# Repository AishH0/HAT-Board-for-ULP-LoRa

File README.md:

# ULP LoRa HAT PCB Design

The ULP LoRa HAT PCB is designed for 5V sensors to integrate with the ULP LoRa board. However, since the ULP LoRa only provides a 3.3V output voltage, 5V sensors cannot be directly integrated. This issue can be resolved by using a buck-boost converter or a boost converter circuit. In this PCB, the voltage is stepped up from 3.3V to 5V using a boost converter circuit with a TPS61202 IC. Level shifter (SN74LV1T34) is added for UART and GPIO peripherals.

# PCB Testing

- Short circuit test using Multimeter; No short ckt in the PCB.
- Provided 3.3V to the input side and Output voltage is noted (Needed output voltage is 5V); The output voltage is 6.5V.
- Varying the input voltage from 1V to 5V and the output voltage is
noted; The output voltage of the boost converter circuit is varying upto
6.5V (from the datasheet TPS61202 IC provides constant 5V.)
 - Varying the inductors and the output voltage is noted; Variable output
voltage is obtained.The PCB was modified using the TPS6120xEVM-179 datasheet. By varying the input voltage from 1V to 5V, the output voltage remains constant at 6.6V.

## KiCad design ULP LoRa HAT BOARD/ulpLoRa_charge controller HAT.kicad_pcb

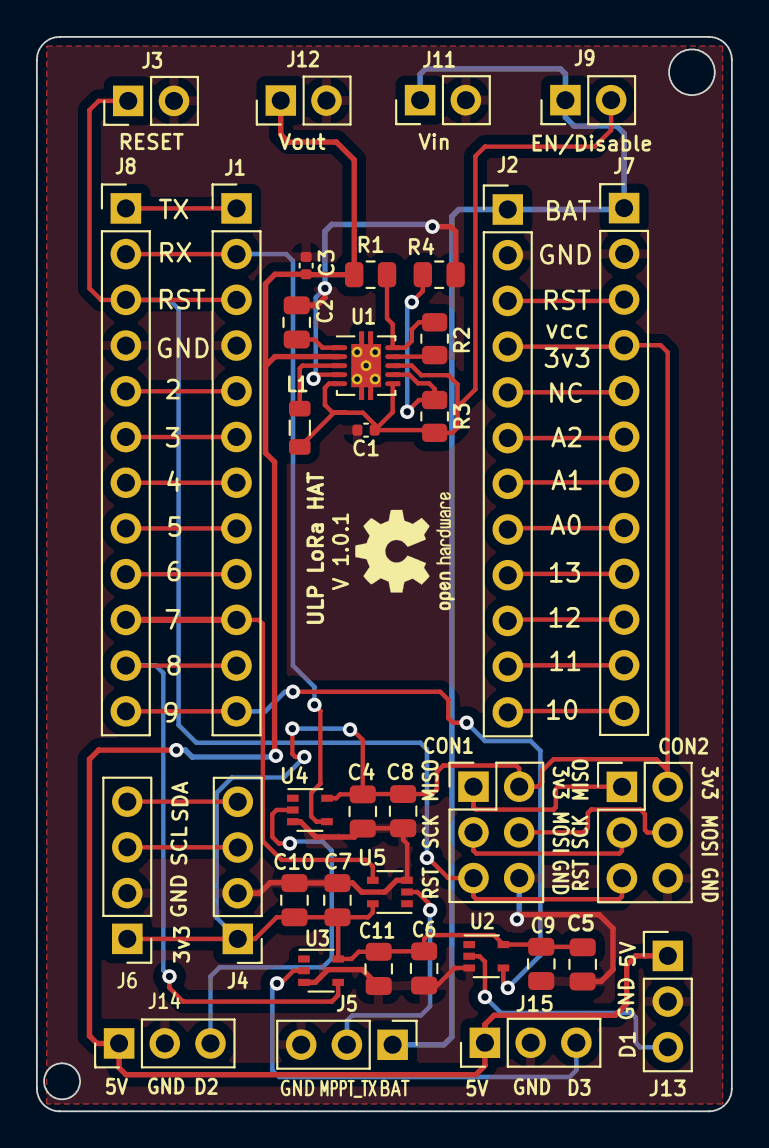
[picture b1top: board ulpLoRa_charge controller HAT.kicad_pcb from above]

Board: 2 copper layers, 38.6 x 59.7 mm, 38 parts (0 on the bottom side), 38 nets.

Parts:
C1, C3: 10uF; C_0402_1005Metric
C2, C4, C7, C9, C11: 0.1uF; C_0805_2012Metric
C5, C6, C8, C10: 1uF; C_0805_2012Metric
CON1, CON2: AVR-ISP-6; PinHeader_2x03_P2.54mm_Vertical
J1, J2: Conn_01x12; PinHeader_1x12_P2.54mm_Vertical
J3: RESET; PinHeader_1x02_P2.54mm_Vertical
J4, J6: I2C; PinHeader_1x04_P2.54mm_Vertical
J5, J13, J14, J15: Conn_01x03; PinHeader_1x03_P2.54mm_Vertical
J7, J8: Conn_01x12_Pin; PinHeader_1x12_P2.54mm_Vertical
J9: EN/Disable; PinHeader_1x02_P2.54mm_Vertical
J11: Vin; PinHeader_1x02_P2.54mm_Vertical
J12: Vout; PinHeader_1x02_P2.54mm_Vertical
L1: 2.2uH; L_0805_2012Metric
R1: 4.22M; R_0805_2012Metric
R2: 470K; R_0805_2012Metric
R3: 2.15M; R_0805_2012Metric
R4: 240K; R_0805_2012Metric
U1: TPS61202DRC; Texas_S-PVSON-N10_ThermalVias
U2, U3, U4, U5: SN74LV1T34DCK; SOT-353_SC-70-5
lg1: OSHW-Logo2_7.3x6mm_SilkScreen

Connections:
/5V: C3.2, J12.1, J13.1, J14.1, J15.1, R1.1, U1.2 (VOUT)
/7: J1.10, J8.10, U5.4 (Y)
/8: J1.11, J8.11, U3.4 (Y)
/9: J1.12, J8.12, U2.4 (Y)
/BAT: J2.1, J5.1, J7.1, J9.1, J11.1
/D1: J13.3, U2.2 (A)
/D2: J14.3, U4.2 (A)
/D3: J15.3, U3.2 (A)
/MISO: CON1.1, CON2.1
/MOSI: CON1.4, CON2.4
/MPPT_TX: J5.2, U5.2 (A)
/RST: CON1.5, CON2.5, J1.3, J3.1, J8.3
/RX: J1.2, J8.2, U4.4 (Y)
/SCK: CON1.3, CON2.3
/SCL: J4.3, J6.3
/SDA: J4.4, J6.4
/VCC: C4.1, C5.1, C6.1, C7.1, C8.1, C9.1, C10.1, C11.1, CON1.2, CON2.2, J2.4, J4.1, J6.1, J7.4, U2.5 (VCC), U3.5 (VCC), U4.5 (VCC), U5.5 (VCC)
GND: C1.1, C2.2, C3.1, C4.2, C5.2, C6.2, C7.2, C8.2, C9.2, C10.2, C11.2, CON1.6, CON2.6, J1.4, J2.2, J3.2, J4.2, J5.3, J6.2, J7.2, J8.4, J11.2, J12.2, J13.2, J14.2, J15.2, R2.2, R4.2, U1.4 (PGND), U1.9 (GND), U2.3 (GND), U3.3 (GND), U4.3 (GND), U5.3 (GND)
unnamed: J1.1, J8.1
unnamed: J1.5, J8.5
unnamed: J1.6, J8.6
unnamed: J1.7, J8.7
unnamed: J1.8, J8.8
unnamed: J1.9, J8.9
unnamed: J2.3, J7.3
unnamed: J2.5, J7.5
unnamed: J2.6, J7.6
unnamed: J2.7, J7.7
unnamed: J2.8, J7.8
unnamed: J2.9, J7.9
unnamed: J2.10, J7.10
unnamed: J2.11, J7.11
unnamed: J2.12, J7.12
unnamed: C1.2, J9.2, L1.1, R3.1, U1.5 (VIN), U1.6 (EN), U1.8 (PS)
unnamed: R1.2, R2.1, U1.10 (FB)
unnamed: L1.2, U1.3 (L)
unnamed: R3.2, R4.1, U1.7 (UVLO)
unnamed: C2.1, U1.1 (VAUX)

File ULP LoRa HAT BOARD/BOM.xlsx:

BILL OF MATERIALS
Item | Quantity | Reference | Value | PART TYPE | PCB Footprint | Manufacturer Part Number | Manfacturer Name | To be Procured by PCB Power | Remarks | Link
1 | 1 | U1 | IC REG BOOST 5V 1.2A 10VSON | Boost Converter | Boost Converter_SMD:10-VFDFN Exposed Pad | TPS61202DRCT | Texas Instruments | Yes |  | https://www.digikey.in/en/products/detail/texas-instruments/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
2 | 4 | U2, U3,U4, U5 | IC BUF NON-INVERT 5.5V SC70-5 | CMOS Logic level shifter | CMOS Logic Level shifter_SMD:SC-70-5 | SN74LV1T34DCKR | Texas Instruments | Yes |  | https://www.digikey.in/en/products/detail/texas-instruments/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
3 | 5 | C2, C4, C7, C9, C11 | 0.1 uF/10 V | Capacitor | Capacitor_SMD:C_0805_2012 Metric | C0805X104K8RACAUTO | KMET | yes |  | https://in.element14.com/kemet/c0805x104k8racauto/cap-mlcc-a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
4 | 4 | C6, C8, C5, C10 | 1 uF/10 V | Capacitor | Capacitor_SMD:C_0805_2012 Metric | C0805C105K8NACTU | KMET | yes |  | https://in.element14.com/kemet/c0805c105k8nactu/cap-1-f-10v-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
5 | 2 | C1, C3 | 10 uF/6.3 V | Capacitor | Capacitor_SMD:C_0402_1005 Metric | 490-GRM155R60J106ME05DCT-ND - Cut Tape (CT) | YAGEO | yes |  | https://www.digikey.in/en/products/detail/murata-electronics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
6 | 1 | R1 | 4.22 MOhms | Resistor | Resistor_SMD:R_0805_2012 Metric | CRCW08054M22FKEA | VISHAY | yes |  | https://www.mouser.in/ProductDetail/Vishay-Dale/CRCW08054M22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
7 | 1 | R2 | 470 Kohm | Resistor | Resistor_SMD:R_0805_2012 Metric | RCS0805470KJNEA | VISHAY | yes |  | https://www.mouser.in/ProductDetail/Vishay-Dale/RCS0805470KJ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
8 | 1 | R3 | 2.15 Mohm | Resistor | Resistor_SMD:R_0805_2012 Metric | CRCW08052M15FKEA | VISHAY | yes |  | https://www.mouser.in/ProductDetail/Vishay-Dale/CRCW08052M15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
9 | 1 | R4 | 240 Kohm | Resistor | Resistor_SMD:R_0805_2012 Metric | ERJ-HP6D2403V | Panasonic | yes |  | https://www.mouser.in/ProductDetail/Panasonic/ERJ-HP6D2403V?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
10 | 1 | L1 | 2.2 uH | Inductor | Inductor_SMD:I_0805_20212Metric | LQM21PN2R2MCHD | MURATA | yes |  | https://in.element14.com/murata/lqm21pn2r2mchd/inductor-2-2u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
11 | 4 | J1, J2, J7, J8 | ~ | Connector Pin header 1*12 |  |  |  | yes | DNP
12 | 2 | CON1, CON2 | ~ | Connector pin header 2*3 |  |  |  | yes | DNP
13 | 2 | J6, J4 | ~ | Connector pin header 1*4 |  |  |  | yes | DNP
14 | 4 | J5, J13, J14, J15 | ~ | Connector Pin header 1*3 |  |  |  | yes | DNP
15 | 4 | J3, J9, J11, J12 | ~ | Connector Pin header 1*2 |  |  |  | yes | DNP

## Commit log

2024-01-22 Ki CAd design file of ULP LoRa HAT
    Ki CAd design file of ULP LoRa HAT
